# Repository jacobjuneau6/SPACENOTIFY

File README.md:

# SPACENOTIFY
SPACENOTIFY is a desktop dashboard that shows all space related activites including Launches, Landing and EVAs through the Launch Library 2 API.
# WHY
I designed SPACENOTIFY because I often can not look at my phone to check upcoming launches and I never want to miss one so this can sit on mydesk and as it has no controls can not be a distraction like a phone.
# Pictures

# BOM
| Name | Purpose | Quantity | Total Cost (USD) | Link | Distributor |
| --- | --- | --- | --- | --- | --- |
| GRM188R60J106KE47D 10uF capacitor | power filtering | 2 | 0.22 | https://www.digikey.com/en/products/detail/murata-electronics/GRM188R60J106KE47D/5797506 | Digikey |
| RC0402FR-075K1L 5.1k resistor | controll usb-c pd voltage | 2 | 0.20 | https://www.digikey.com/en/products/detail/yageo/RC0402FR-075K1L/726624 | Digikey |
| CX90BW1-24P1 USB c connector | power + data | 1 | 2.99 | https://www.digikey.com/en/products/detail/hirose-electric-co-ltd/CX90BW1-24P1/22566049?s=N4IgTCBcDaIMIA0CcAGAQgdQIwFowBYAFLEAXQF8g | Digikey |
| SKRPABE010 button | to trigger boot and reset the esp32 | 2 | 0.42 | https://www.digikey.com/en/products/detail/alps-alpine/SKRPABE010/18768948 | Digikey |
| TLV1117-33IDCYR | LDO voltage regulator | 1 | 0.45 | https://www.digikey.com/en/products/detail/texas-instruments/TLV1117-33IDCYR/1216719 | Digikey |
| ESP32-S3-WROOM-1-N8R2 | Main MCU | 1 | 5.71 | https://www.digikey.com/en/products/detail/espressif-systems/ESP32-S3-WROOM-1-N8R2/15200058 | Digikey |
| Touch sensor | to allow UI interaction | 10 | 1.66 | https://www.aliexpress.us/item/3256806056841370.html?utparam-url=scene%3Asearch%7Cquery_from%3A%7Cx_object_id%3A1005006243156122%7C_p_origin_prod%3A&search_p4p_id=20260409181228570240878276160000137350_2 | Aliexpress |
| 1.8in LCD | Displays main info | 1 | 2.88 | https://www.aliexpress.us/item/3256805953674718.html?utparam-url=scene%3Asearch%7Cquery_from%3A%7Cx_object_id%3A1005006139989470%7C_p_origin_prod%3A | Aliexpress |
| PCB | Holds the display and esp32 | 1 | 5.00 |  | PCBWAY |
| I2c display | shows the info | 1 | 1.99 | https://www.aliexpress.us/item/3256805899077405.html?utparam-url=scene%3Asearch%7Cquery_from%3A%7Cx_object_id%3A1005006085392157%7C_p_origin_prod%3A&search_p4p_id=20260331193731576094732592880001235155_1 | Aliexpress |

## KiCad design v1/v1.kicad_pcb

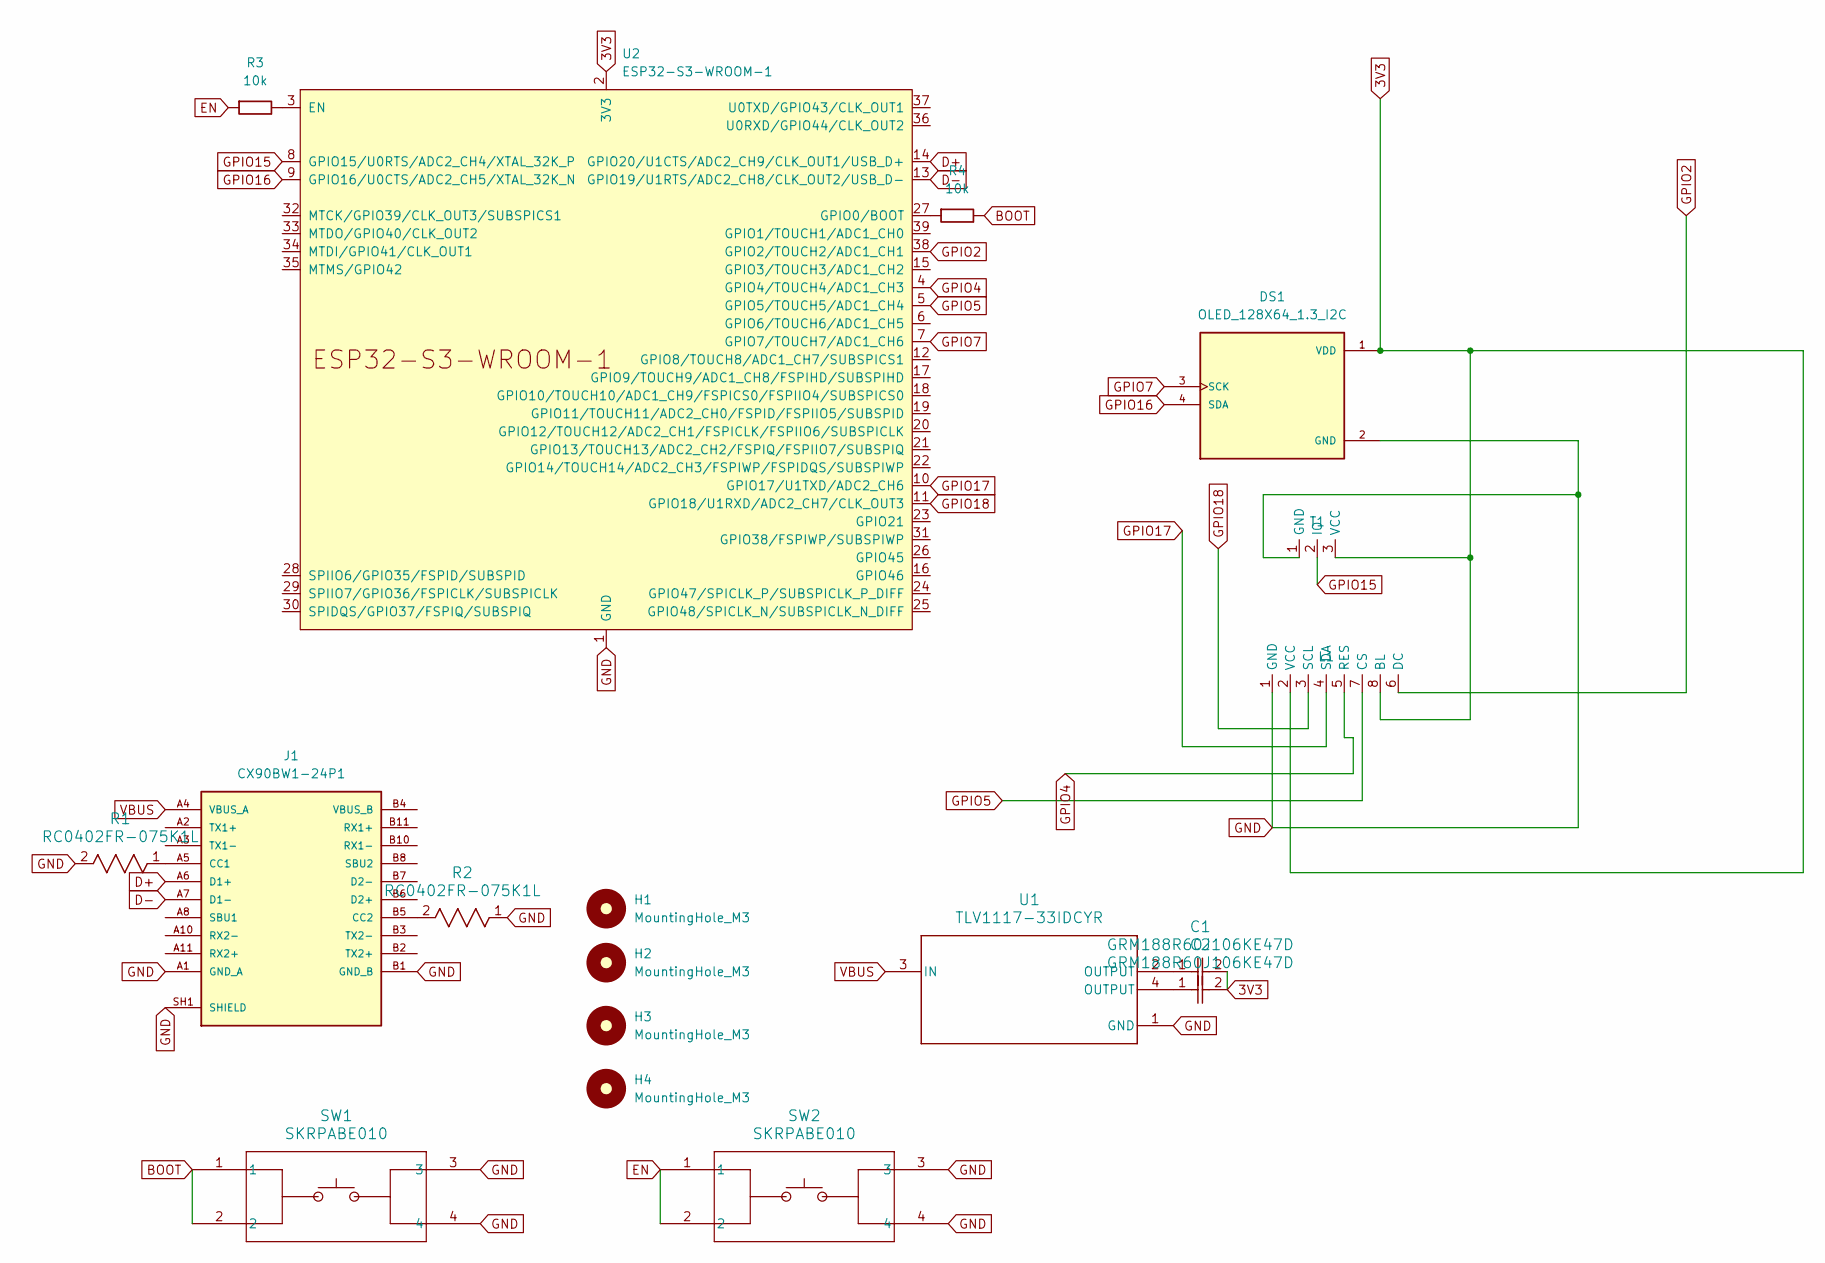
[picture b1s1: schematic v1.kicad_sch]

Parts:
C1, C2: GRM188R60J106KE47D; CAP_GRM188_1608_MUR
DS1: OLED_128X64_1.3_I2C; LCD_OLED_128X64_1.3_I2C; PARTREV NA
H1, H2, H3, H4: MountingHole_M3; MountingHole_3.2mm_M3
J1: CX90BW1-24P1; HIROSE_CX90BW1-24P1; PARTREV 24.05.01; DigiKey_Part_Number 26-CX90BW1-24P1CT-ND
L1: PinHeader_1x08_P2.54mm_Vertical
R1, R2: RC0402FR-075K1L; RC0402N_YAG
R3, R4: 10k; R_Axial_DIN0207_L6.3mm_D2.5mm_P10.16mm_Horizontal
SW1, SW2: SKRPABE010; SW4_SKRPABE010_ALPS
T1: PinHeader_1x03_P2.54mm_Vertical
U1: TLV1117-33IDCYR; DCY0004A_L
U2: ESP32-S3-WROOM-1

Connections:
3V3: C1.2, C2.2, DS1.1 (VDD), L1.2 (VCC), L1.8 (BL), T1.3 (VCC), U2.2 (3V3)
BOOT: R4.2, SW1.1, SW1.2
D+: J1.A6 (D1+), U2.14 (GPIO20/U1CTS/ADC2_CH9/CLK_OUT1/USB_D+)
D-: J1.A7 (D1-), U2.13 (GPIO19/U1RTS/ADC2_CH8/CLK_OUT2/USB_D-)
EN: R3.1, SW2.1, SW2.2
GND: DS1.2 (GND), J1.A1 (GND_A), J1.A12 (GND_A), J1.B1 (GND_B), J1.B12 (GND_B), J1.SH1 (SHIELD), J1.SH2 (SHIELD), J1.SH3 (SHIELD), J1.SH4 (SHIELD), L1.1 (GND), R1.2, R2.1, SW1.3, SW1.4, SW2.3, SW2.4, T1.1 (GND), U1.1 (GND), U2.1 (GND), U2.40 (GND), U2.41 (GND)
GPIO2: L1.6 (DC), U2.38 (GPIO2/TOUCH2/ADC1_CH1)
GPIO4: L1.5 (RES), U2.4 (GPIO4/TOUCH4/ADC1_CH3)
GPIO5: L1.7 (CS), U2.5 (GPIO5/TOUCH5/ADC1_CH4)
GPIO7: DS1.3 (SCK), U2.7 (GPIO7/TOUCH7/ADC1_CH6)
GPIO15: T1.2 (IO), U2.8 (GPIO15/U0RTS/ADC2_CH4/XTAL_32K_P)
GPIO16: DS1.4 (SDA), U2.9 (GPIO16/U0CTS/ADC2_CH5/XTAL_32K_N)
GPIO17: L1.4 (SDA), U2.10 (GPIO17/U1TXD/ADC2_CH6)
GPIO18: L1.3 (SCL), U2.11 (GPIO18/U1RXD/ADC2_CH7/CLK_OUT3)
unnamed: C1.1, U1.2 (OUTPUT)
unnamed: C2.1, U1.4 (OUTPUT)
unnamed: J1.A5 (CC1), R1.1
unnamed: J1.B5 (CC2), R2.2
unnamed: R3.2, U2.3 (EN)
unnamed: R4.1, U2.27 (GPIO0/BOOT)
VBUS: J1.A4 (VBUS_A), J1.A9 (VBUS_A), U1.3 (IN)
VBUS_B: J1.B4 (VBUS_B), J1.B9 (VBUS_B)

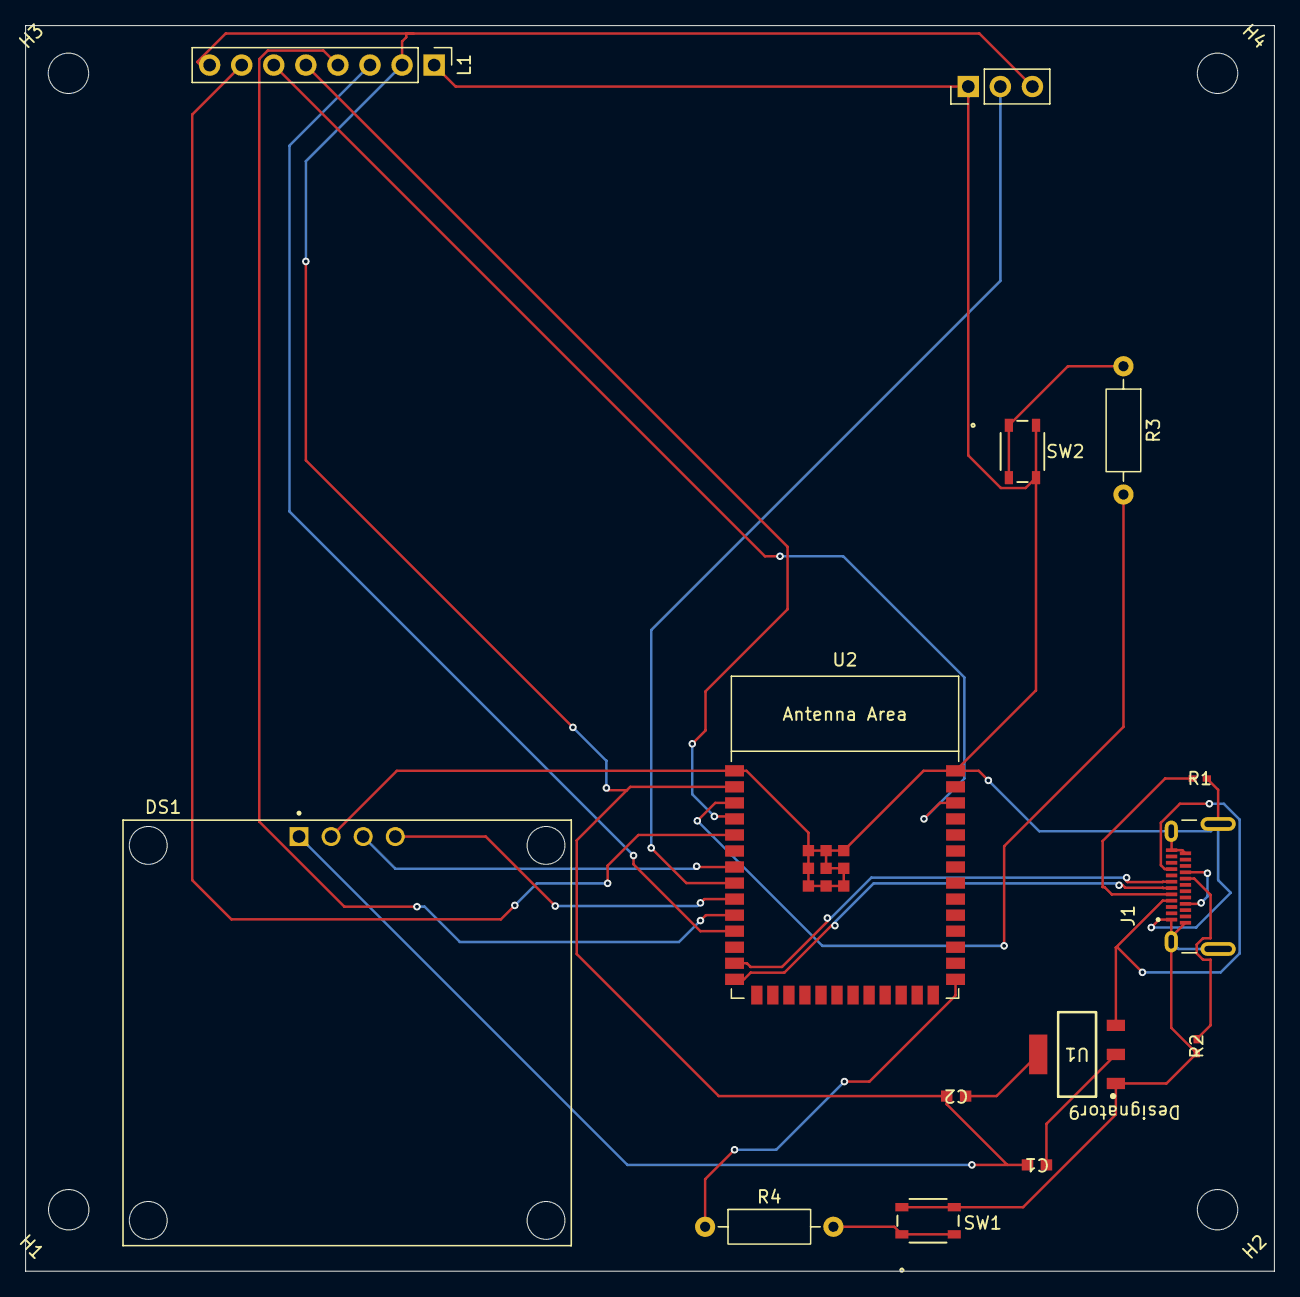
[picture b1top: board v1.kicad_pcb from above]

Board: 2 copper layers, 98.9 x 98.6 mm, 18 parts (0 on the bottom side), 22 nets.

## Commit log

2026-04-04 ADD FILES
2026-04-04 pictues&readme
2026-04-10 code, new pcb and bom
2026-04-10 picture of routes
2026-04-10 pictures
2026-04-10 new PCB schematic, readme, BOM
2026-04-10 readme
